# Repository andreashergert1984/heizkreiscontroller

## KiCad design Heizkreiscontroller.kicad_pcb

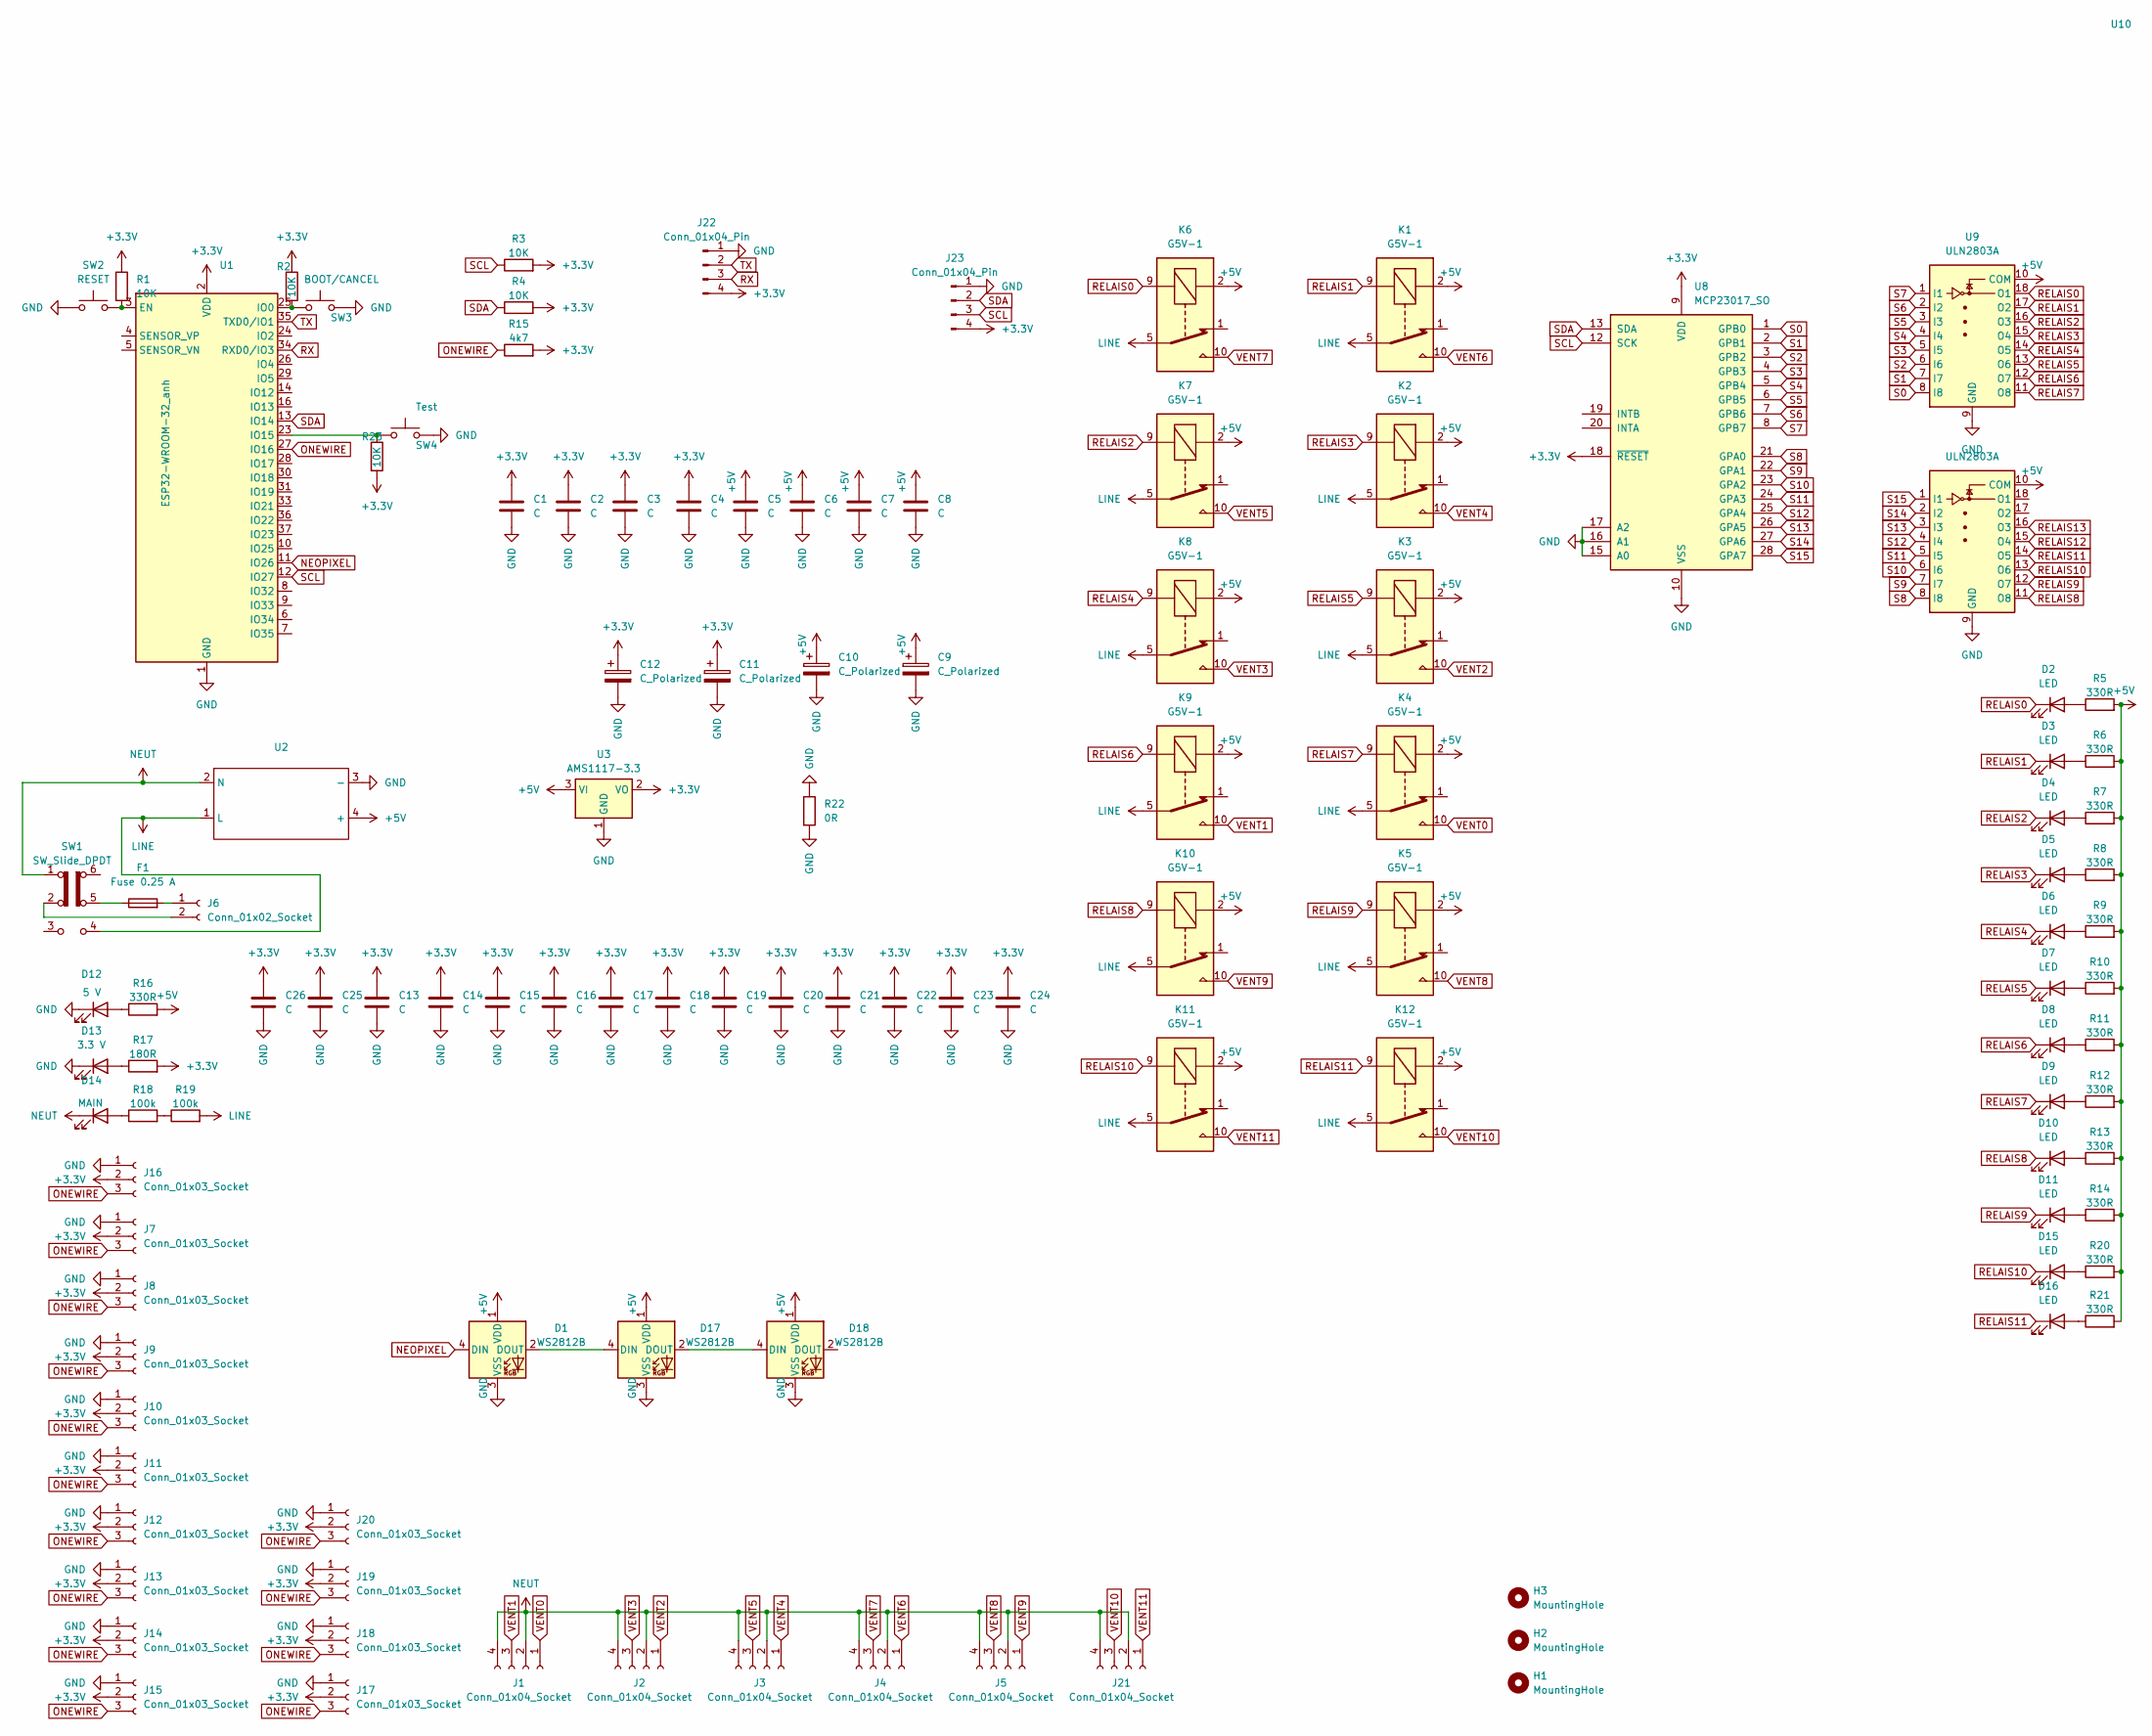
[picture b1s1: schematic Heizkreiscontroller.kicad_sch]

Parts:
C1, C2, C3, C4, C5, C6, C7, C8, C13, C14, C15, C16, C17, C18, C19, C20, C21, C22, C23, C24, C25, C26: C; C_1210_3225Metric_Pad1.33x2.70mm_HandSolder
C9, C10, C11, C12: C_Polarized; CP_Radial_D8.0mm_P3.50mm
D1, D17, D18: WS2812B; LED_WS2812B_PLCC4_5.0x5.0mm_P3.2mm
D2, D3, D4, D5, D6, D7, D8, D9, D10, D11, D15, D16: LED; LED_0805_2012Metric_Pad1.15x1.40mm_HandSolder
D12: 5 V; LED_0805_2012Metric_Pad1.15x1.40mm_HandSolder
D13: 3.3 V; LED_0805_2012Metric_Pad1.15x1.40mm_HandSolder
D14: MAIN; LED_0805_2012Metric_Pad1.15x1.40mm_HandSolder
F1: Fuse 0.25 A; Fuseholder_Cylinder-5x20mm_Schurter_0031_8201_Horizontal_Op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
H1, H2, H3: MountingHole; MountingHole_3.2mm_M3
J1, J2, J3, J4, J5, J21: Conn_01x04_Socket; TLM-004-4PIN
J6: Conn_01x02_Socket; TLM-004-2PIN
J7, J8, J9, J10, J11, J12, J13, J14, J15, J16, J17, J18, J19, J20: Conn_01x03_Socket; TerminalBlock_KaiFeng_KF141R-3_1x03_P2.54mm
J22, J23: Conn_01x04_Pin; PinHeader_1x04_P2.54mm_Vertical
K1, K2, K3, K4, K5, K6, K7, K8, K9, K10, K11, K12: G5V-1; Relay_SPDT_Omron_G5V-1
R1, R2, R3, R4, R23: 10K; R_0805_2012Metric_Pad1.20x1.40mm_HandSolder
R5, R6, R7, R8, R9, R10, R11, R12, R13, R14, R16, R20, R21: 330R; R_0805_2012Metric_Pad1.20x1.40mm_HandSolder
R15: 4k7; R_0805_2012Metric_Pad1.20x1.40mm_HandSolder
R17: 180R; R_0805_2012Metric_Pad1.20x1.40mm_HandSolder
R18, R19: 100k; R_0805_2012Metric_Pad1.20x1.40mm_HandSolder
R22: 0R; R_2512_6332Metric
SW1: SW_Slide_DPDT; SW_PUSH_E-Switch_FS5700DP_DPDT_anh
SW2: RESET; SW_Push_SPST_NO_Alps_SKRK
SW3: BOOT/CANCEL; SW_Push_SPST_NO_Alps_SKRK
SW4: Test; SW_Push_SPST_NO_Alps_SKRK
U1: ESP32-WROOM-32_anh
U2: AC-DC-Module12v5v
U3: AMS1117-3.3; SOT-223-3_TabPin2
U8: MCP23017_SO; SOIC-28W_7.5x17.9mm_P1.27mm
U9, U10: ULN2803A; SOIC-18W_7.5x11.6mm_P1.27mm

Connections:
+3.3V: C1.2, C2.2, C3.2, C4.2, C11.1, C12.1, C13.2, C14.2, C15.2, C16.2, C17.2, C18.2, C19.2, C20.2, C21.2, C22.2, C23.2, C24.2, C25.2, C26.2, J7.2, J8.2, J9.2, J10.2, J11.2, J12.2, J13.2, J14.2, J15.2, J16.2, J17.2, J18.2, J19.2, J20.2, J22.4, J23.4, R1.1, R2.1, R3.2, R4.2, R15.2, R17.2, R23.2, U1.2 (VDD), U3.2 (VO), U8.9 (VDD), U8.18 (~RESET)
+5V: C5.2, C6.2, C7.2, C8.2, C9.1, C10.1, D1.1 (VDD), D17.1 (VDD), D18.1 (VDD), K1.2, K2.2, K3.2, K4.2, K5.2, K6.2, K7.2, K8.2, K9.2, K10.2, K11.2, K12.2, R5.2, R6.2, R7.2, R8.2, R9.2, R10.2, R11.2, R12.2, R13.2, R14.2, R16.2, R20.2, R21.2, U2.4 (+), U3.3 (VI), U9.10 (COM), U10.10 (COM)
GND: C1.1, C2.1, C3.1, C4.1, C5.1, C6.1, C7.1, C8.1, C9.2, C10.2, C11.2, C12.2, C13.1, C14.1, C15.1, C16.1, C17.1, C18.1, C19.1, C20.1, C21.1, C22.1, C23.1, C24.1, C25.1, C26.1, D1.3 (VSS), D12.1 (K), D13.1 (K), D17.3 (VSS), D18.3 (VSS), J7.1, J8.1, J9.1, J10.1, J11.1, J12.1, J13.1, J14.1, J15.1, J16.1, J17.1, J18.1, J19.1, J20.1, J22.1, J23.1, R22.1, R22.2, SW2.1, SW3.2, SW4.2, U1.1 (GND), U1.15 (GND), U1.38 (GND), U1.39 (GND), U2.3 (-), U3.1 (GND), U8.10 (VSS), U8.15 (A0), U8.16 (A1), U8.17 (A2), U9.9 (GND), U10.9 (GND)
LINE: K1.5, K1.6, K2.5, K2.6, K3.5, K3.6, K4.5, K4.6, K5.5, K5.6, K6.5, K6.6, K7.5, K7.6, K8.5, K8.6, K9.5, K9.6, K10.5, K10.6, K11.5, K11.6, K12.5, K12.6, R19.2, SW1.4 (A), U2.1 (L)
NEOPIXEL: D1.4 (DIN), U1.11 (IO26)
NEUT: D14.1 (K), J1.2, J1.4, J2.2, J2.4, J3.2, J3.4, J4.2, J4.4, J5.2, J5.4, J21.2, J21.4, SW1.1 (A), U2.2 (N)
unnamed: D1.2 (DOUT), D17.4 (DIN)
unnamed: D2.2 (A), R5.1
unnamed: D3.2 (A), R6.1
unnamed: D4.2 (A), R7.1
unnamed: D5.2 (A), R8.1
unnamed: D6.2 (A), R9.1
unnamed: D7.2 (A), R10.1
unnamed: D8.2 (A), R11.1
unnamed: D9.2 (A), R12.1
unnamed: D10.2 (A), R13.1
unnamed: D11.2 (A), R14.1
unnamed: D12.2 (A), R16.1
unnamed: D13.2 (A), R17.1
unnamed: D14.2 (A), R18.1
unnamed: D15.2 (A), R20.1
unnamed: D16.2 (A), R21.1
unnamed: D17.2 (DOUT), D18.4 (DIN)
unnamed: F1.1, SW1.5 (B)
unnamed: F1.2, J6.1
unnamed: J6.2, SW1.2 (B)
unnamed: R18.2, R19.1
unnamed: R1.2, SW2.2, U1.3 (EN)
unnamed: R2.2, SW3.1, U1.25 (IO0)
unnamed: R23.1, SW4.1, U1.23 (IO15)
ONEWIRE: J7.3, J8.3, J9.3, J10.3, J11.3, J12.3, J13.3, J14.3, J15.3, J16.3, J17.3, J18.3, J19.3, J20.3, R15.1, U1.27 (IO16)
RELAIS0: D2.1 (K), K6.9, U9.18 (O1)
RELAIS1: D3.1 (K), K1.9, U9.17 (O2)
RELAIS2: D4.1 (K), K7.9, U9.16 (O3)
RELAIS3: D5.1 (K), K2.9, U9.15 (O4)
RELAIS4: D6.1 (K), K8.9, U9.14 (O5)
RELAIS5: D7.1 (K), K3.9, U9.13 (O6)
RELAIS6: D8.1 (K), K9.9, U9.12 (O7)
RELAIS7: D9.1 (K), K4.9, U9.11 (O8)
RELAIS8: D10.1 (K), K10.9, U10.11 (O8)
RELAIS9: D11.1 (K), K5.9, U10.12 (O7)
RELAIS10: D15.1 (K), K11.9, U10.13 (O6)
RELAIS11: D16.1 (K), K12.9, U10.14 (O5)
RELAIS12: U10.15 (O4)
RELAIS13: U10.16 (O3)
RX: J22.3, U1.34 (RXD0/IO3)
S0: U8.1 (GPB0), U9.8 (I8)
S1: U8.2 (GPB1), U9.7 (I7)
S2: U8.3 (GPB2), U9.6 (I6)
S3: U8.4 (GPB3), U9.5 (I5)
S4: U8.5 (GPB4), U9.4 (I4)
S5: U8.6 (GPB5), U9.3 (I3)
S6: U8.7 (GPB6), U9.2 (I2)
S7: U8.8 (GPB7), U9.1 (I1)
S8: U8.21 (GPA0), U10.8 (I8)
S9: U8.22 (GPA1), U10.7 (I7)
S10: U8.23 (GPA2), U10.6 (I6)
S11: U8.24 (GPA3), U10.5 (I5)
S12: U8.25 (GPA4), U10.4 (I4)
S13: U8.26 (GPA5), U10.3 (I3)
S14: U8.27 (GPA6), U10.2 (I2)
S15: U8.28 (GPA7), U10.1 (I1)
SCL: J23.3, R3.1, U1.12 (IO27), U8.12 (SCK)
SDA: J23.2, R4.1, U1.13 (IO14), U8.13 (SDA)
TX: J22.2, U1.35 (TXD0/IO1)
VENT0: J1.1, K4.10
VENT1: J1.3, K9.10
VENT2: J2.1, K3.10
VENT3: J2.3, K8.10
VENT4: J3.1, K2.10
VENT5: J3.3, K7.10
VENT6: J4.1, K1.10
VENT7: J4.3, K6.10
VENT8: J5.3, K5.10
VENT9: J5.1, K10.10
VENT10: J21.3, K12.10
VENT11: J21.1, K11.10

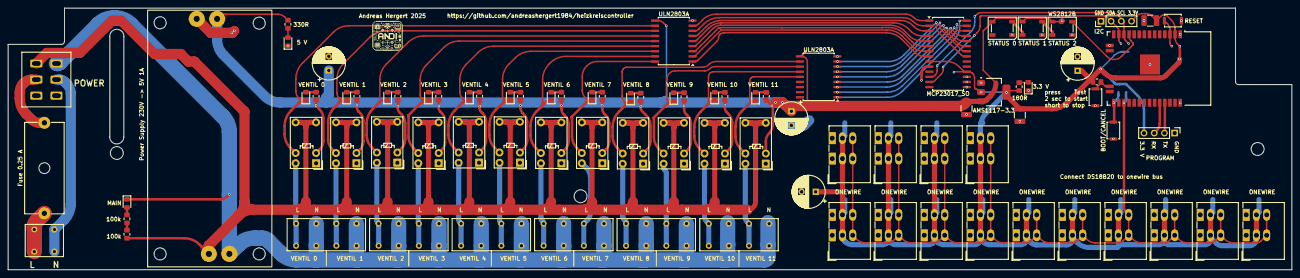
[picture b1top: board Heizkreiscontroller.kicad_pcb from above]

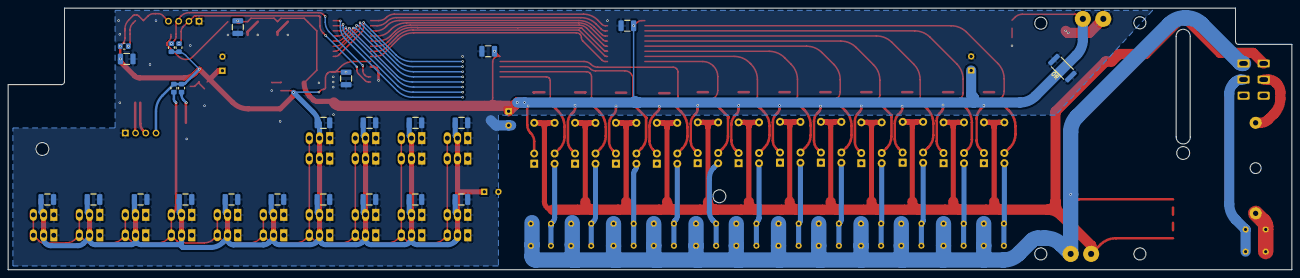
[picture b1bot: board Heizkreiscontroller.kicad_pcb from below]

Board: 2 copper layers, 319.0 x 65.0 mm, 116 parts (25 on the bottom side), 75 nets.
